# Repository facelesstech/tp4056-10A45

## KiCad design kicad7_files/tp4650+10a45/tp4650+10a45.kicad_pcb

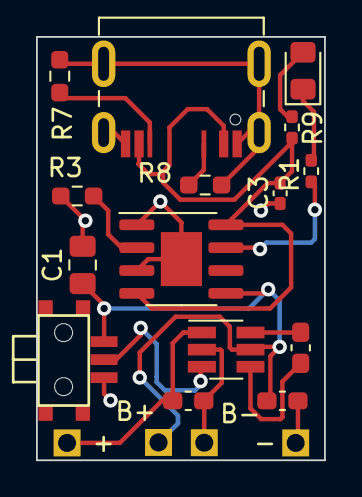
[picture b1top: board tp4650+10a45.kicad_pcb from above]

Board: 2 copper layers, 16.0 x 23.5 mm, 19 parts (0 on the bottom side), 13 nets.

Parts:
+: TestPoint; 1mm_test_point_square
-: TestPoint; 1mm_test_point_square
B+: TestPoint; 1mm_test_point_square
B-: TestPoint; 1mm_test_point_square
C1: 10uF; C_0805_2012Metric_Pad1.18x1.45mm_HandSolder
C2: 2.2uF; C_0603_1608Metric_Pad1.08x0.95mm_HandSolder
C3: 0.1uF; C_0402_1005Metric_Pad0.74x0.62mm_HandSolder
C4, C5: 10uF; C_0603_1608Metric_Pad1.08x0.95mm_HandSolder
D1: RED; LED_0805_2012Metric_Pad1.15x1.40mm_HandSolder
P1: USB_C_Plug; USB_C_Receptacle_JAE_DX07S016JA1R1500
R1: 1k; R_0402_1005Metric_Pad0.72x0.64mm_HandSolder
R3: 10k; R_0603_1608Metric_Pad0.98x0.95mm_HandSolder
R7, R8: 5.1k; R_0603_1608Metric_Pad0.98x0.95mm_HandSolder
R9: R; R_0402_1005Metric_Pad0.72x0.64mm_HandSolder
SW1: SW_DPDT_x2; even_tinier_smd_slide_switch_custom
U1: 10a45; SOT-23-6_10a45
U2: TP4056; SOIC-8-1EP_3.9x4.9mm_P1.27mm_EP2.29x3mm

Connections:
GND: -.1, B-.1, C1.2, C3.2, C4.2, C5.2, P1.A1 (GND), P1.A12 (GND), P1.S1 (SHIELD), R3.2, R7.2, R8.2, SW1.3 (C), U1.2 (GND), U2.1 (TEMP), U2.3 (GND), U2.9 (PP)
unnamed: D1.2 (A), R9.2
unnamed: D1.1 (K), R1.1
unnamed: P1.A8 (SBU1), R7.1
unnamed: P1.B8 (SBU2), R8.1
unnamed: C1.1, C5.1, SW1.1 (A), U1.5 (V_IN), U2.5 (BAT)
unnamed: B+.1, SW1.2 (B), U1.3 (EN)
unnamed: C2.2, U1.6 (C+)
unnamed: C2.1, U1.4 (C-)
unnamed: +.1, C4.1, U1.1 (V_OUT)
unnamed: R3.1, U2.2 (PROG)
unnamed: R1.2, U2.7 (~CHRG)
VIN: C3.1, P1.A4 (VBUS), P1.A9 (VBUS), R9.1, U2.4 (VCC), U2.8 (CE)

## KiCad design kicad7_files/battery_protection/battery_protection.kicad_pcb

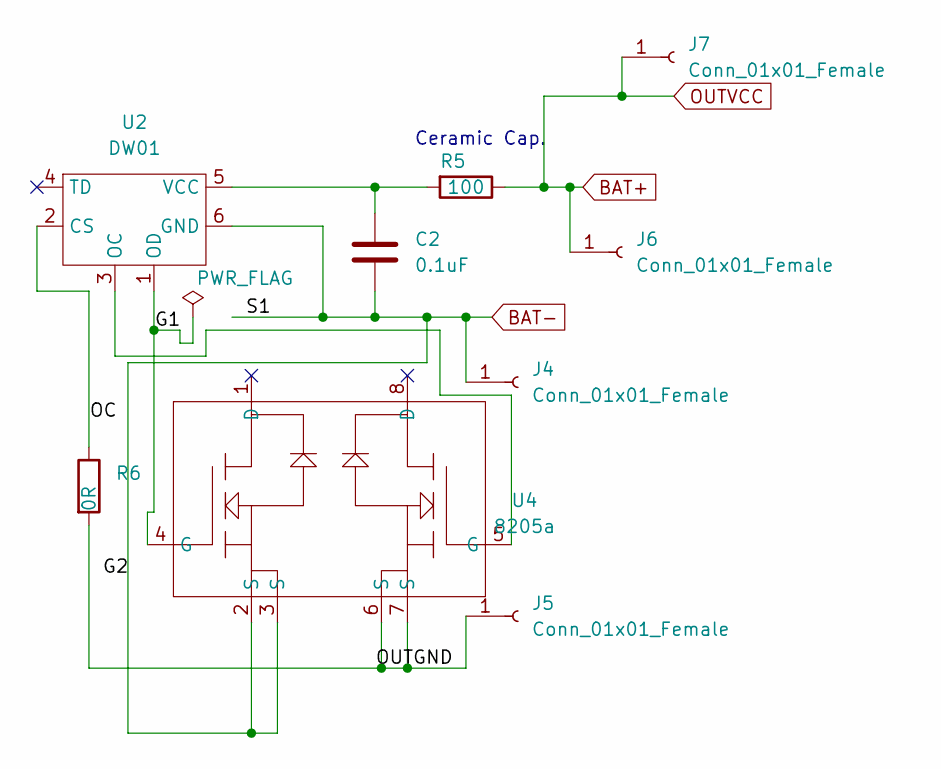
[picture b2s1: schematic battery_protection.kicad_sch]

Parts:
C2: 0.1uF; C_0402_1005Metric_Pad0.74x0.62mm_HandSolder
J4, J5, J6, J7: Conn_01x01_Female; 1mm_test_point_square
R5: 100; R_0402_1005Metric_Pad0.72x0.64mm_HandSolder
R6: 0R; R_0402_1005Metric_Pad0.72x0.64mm_HandSolder
U2: DW01; SOT-23-6_Handsoldering
U4: 8205a; SOT-23-8_Handsoldering_long

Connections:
/G1: U2.1 (OD), U4.4 (G)
/OC: R6.1, U2.2 (CS)
/OUTGND: J5.1, R6.2, U4.6 (S), U4.7 (S)
BAT+: J6.1, J7.1, R5.1
BAT-: C2.2, J4.1, U2.6 (GND), U4.2 (S), U4.3 (S)
unnamed: U2.3 (OC), U4.5 (G)
unnamed: C2.1, R5.2, U2.5 (VCC)

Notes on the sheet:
Ceramic Cap.

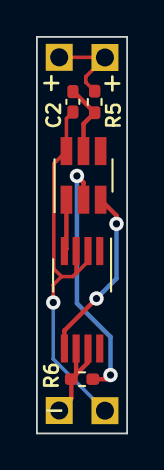
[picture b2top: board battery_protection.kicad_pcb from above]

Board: 2 copper layers, 5.0 x 22.0 mm, 9 parts (0 on the bottom side), 7 nets.

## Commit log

2023-11-11 uploaded both tp4056+10A45 and battery protection board files
2023-11-11 added photo
2023-11-11 added photo to readme
